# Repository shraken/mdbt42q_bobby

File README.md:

# mdbt42q_bobby

A simple break-out board in KiCad EDA for developing Nordic nRF52 BLE projects using the MDBT42 module.  Includes external 32.768 kHz watch crystal and components for internal DC/DC operation.  Breaks out 18 pins from the MDBT42Q module for easy prototyping.

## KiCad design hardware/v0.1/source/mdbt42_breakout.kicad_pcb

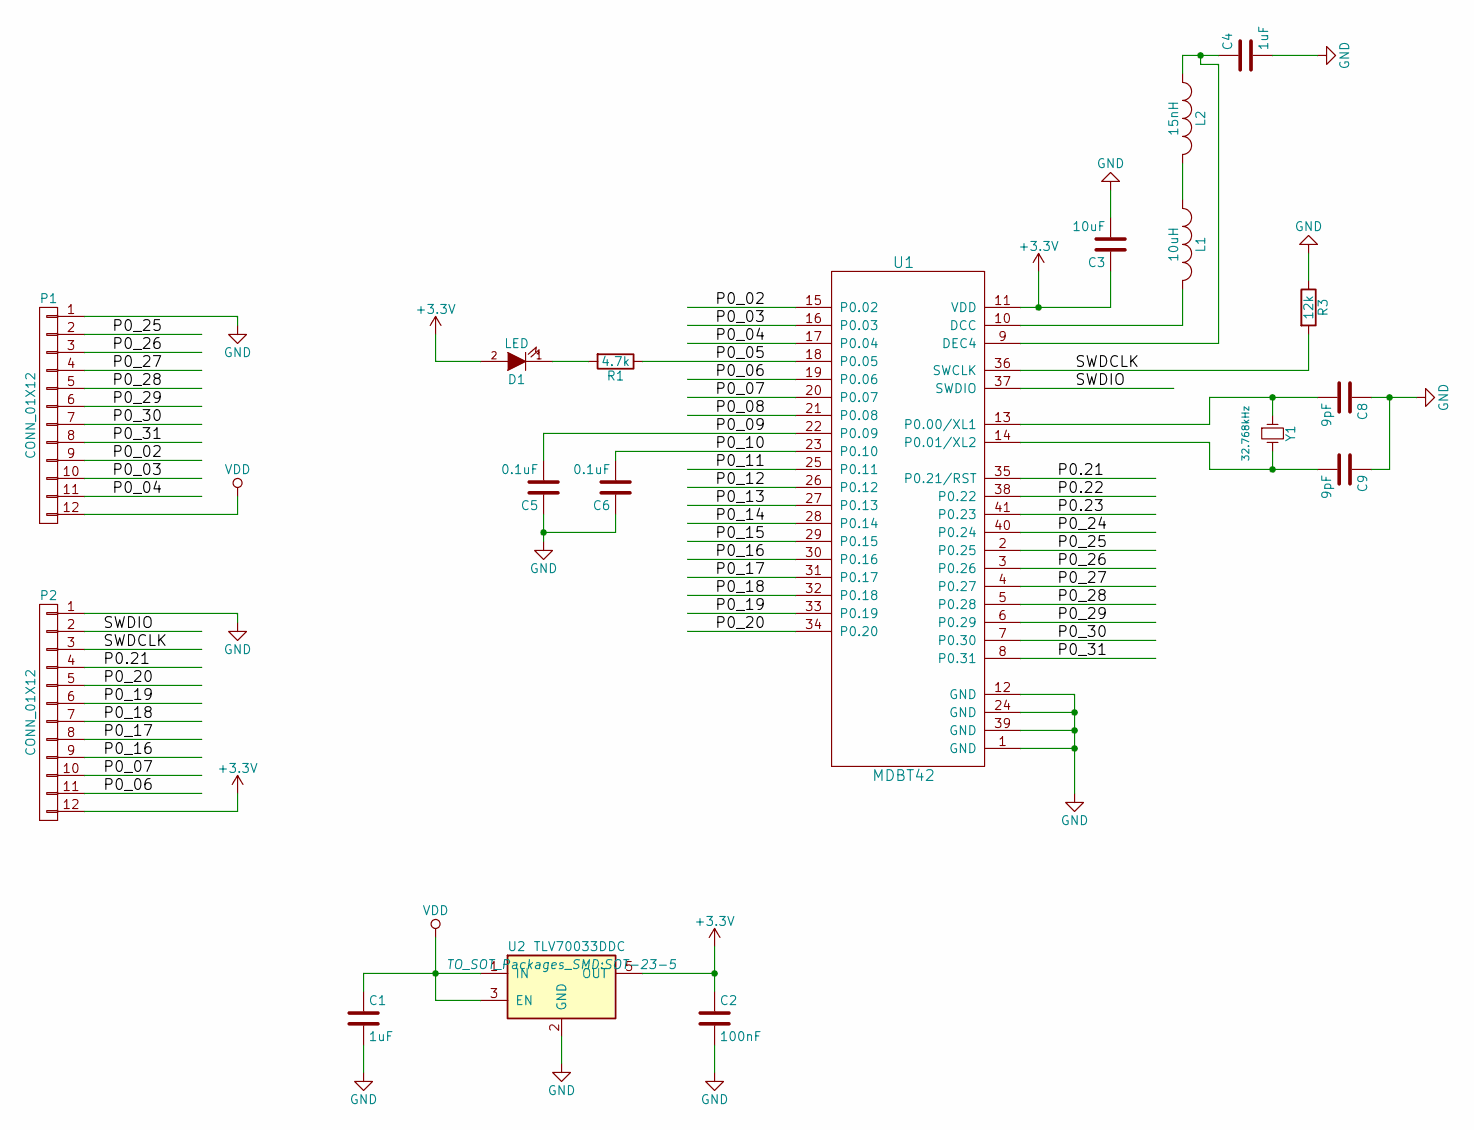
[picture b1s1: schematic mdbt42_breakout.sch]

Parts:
C1, C4: 1uF; C_0603_HandSoldering
C2: 100nF; C_0603_HandSoldering
C3: 10uF; C_0805_HandSoldering
C5, C6: 0.1uF; C_0603_HandSoldering
C8, C9: 9pF; C_0603_HandSoldering
D1: LED; LED_0603
L1: 10uH; C_0603_HandSoldering
L2: 15nH; C_0603_HandSoldering
P1, P2: CONN_01X12; Pin_Header_Straight_1x12
R1: 4.7k; R_0603_HandSoldering
R3: 12k; R_0603_HandSoldering
U1: MDBT42
U2: TLV70033DDC; SOT-23-5
Y1: 32.768kHz; ABS07-LR-32.768kHz-6-1-T

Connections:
+3V3: C2.1, C3.1, D1.2 (A), P2.12, U1.11 (VDD), U2.5 (OUT)
/P0.21: P2.4, U1.35 (P0.21/RST)
/P0.22: U1.38 (P0.22)
/P0.23: U1.41 (P0.23)
/P0_02: P1.9, U1.15 (P0.02)
/P0_03: P1.10, U1.16 (P0.03)
/P0_04: P1.11, U1.17 (P0.04)
/P0_05: R1.1, U1.18 (P0.05)
/P0_06: P2.11, U1.19 (P0.06)
/P0_07: P2.10, U1.20 (P0.07)
/P0_08: U1.21 (P0.08)
/P0_09: C5.2, U1.22 (P0.09)
/P0_10: C6.2, U1.23 (P0.10)
/P0_11: U1.25 (P0.11)
/P0_12: U1.26 (P0.12)
/P0_13: U1.27 (P0.13)
/P0_14: U1.28 (P0.14)
/P0_15: U1.29 (P0.15)
/P0_16: P2.9, U1.30 (P0.16)
/P0_17: P2.8, U1.31 (P0.17)
/P0_18: P2.7, U1.32 (P0.18)
/P0_19: P2.6, U1.33 (P0.19)
/P0_20: P2.5, U1.34 (P0.20)
/P0_24: U1.40 (P0.24)
/P0_25: P1.2, U1.2 (P0.25)
/P0_26: P1.3, U1.3 (P0.26)
/P0_27: P1.4, U1.4 (P0.27)
/P0_28: P1.5, U1.5 (P0.28)
/P0_29: P1.6, U1.6 (P0.29)
/P0_30: P1.7, U1.7 (P0.30)
/P0_31: P1.8, U1.8 (P0.31)
/SWDCLK: P2.3, R3.2, U1.36 (SWCLK)
/SWDIO: P2.2, U1.37 (SWDIO)
GND: C1.2, C2.2, C3.2, C4.2, C5.1, C6.1, C8.1, C9.1, P1.1, P2.1, R3.1, U1.1 (GND), U1.12 (GND), U1.24 (GND), U1.39 (GND), U2.2 (GND)
unnamed: C4.1, L2.1, U1.9 (DEC4)
unnamed: C8.2, U1.13 (P0.00/XL1), Y1.1
unnamed: C9.2, U1.14 (P0.01/XL2), Y1.2
unnamed: D1.1 (K), R1.2
unnamed: L1.1, L2.2
unnamed: L1.2, U1.10 (DCC)
VDD: C1.1, P1.12, U2.1 (IN), U2.3 (EN)

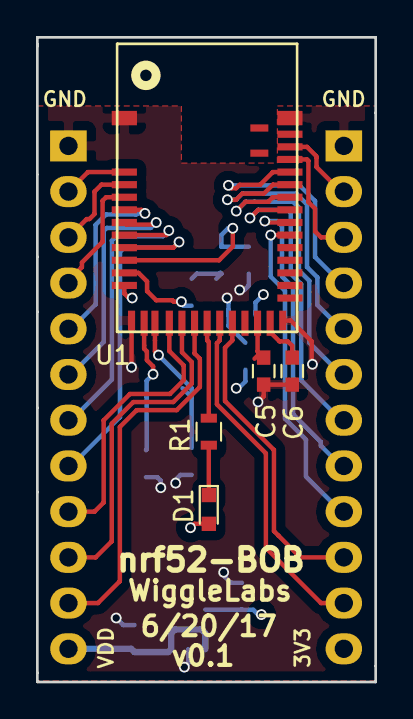
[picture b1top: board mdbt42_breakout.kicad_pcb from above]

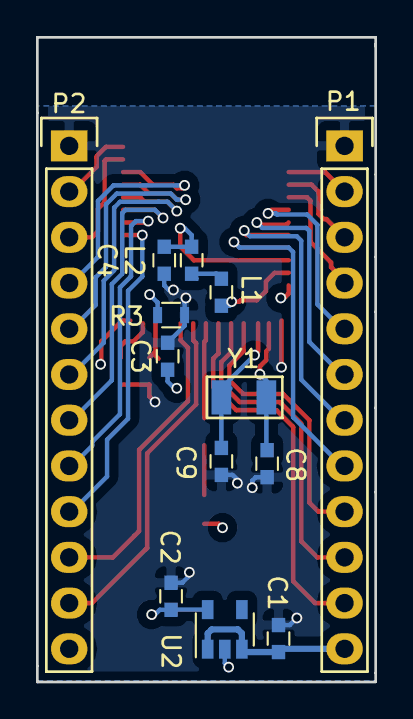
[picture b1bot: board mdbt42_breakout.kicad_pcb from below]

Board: 4 copper layers, 18.8 x 35.8 mm, 18 parts (13 on the bottom side), 32 nets.
